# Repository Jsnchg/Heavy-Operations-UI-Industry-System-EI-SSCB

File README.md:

# Heavy-Operations-UI-Industry-System-EI-SSCB

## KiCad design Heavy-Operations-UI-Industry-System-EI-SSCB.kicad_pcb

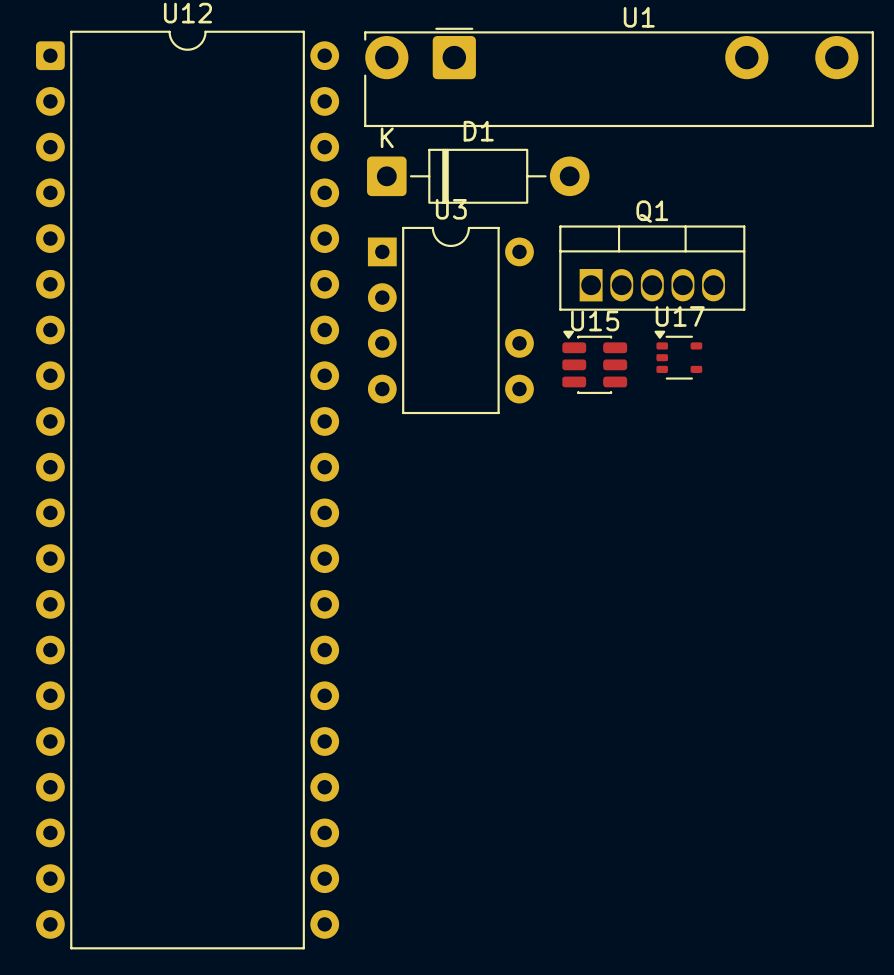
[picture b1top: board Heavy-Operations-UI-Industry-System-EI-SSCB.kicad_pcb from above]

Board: 2 copper layers, 7 parts (0 on the bottom side), 3 nets, no tracks yet.

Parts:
D1: 1N5817; D_DO-41_SOD81_P10.16mm_Horizontal
Q1: IPS6011PBF; TO-220-5_Vertical
U1: 34.81-7048; Finder_34.81
U3: NCP1072P065; DIP-8-N7_W7.62mm
U12: 8080; DIP-40_W15.24mm
U15: LM2665M6; SOT-23-6
U17: TLV172IDCK; SOT-353_SC-70-5

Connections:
unnamed: Q1.3 (VCC), U3.3 (GND), U3.8 (GND)
unnamed: U1.11, U15.1 (V+)
unnamed: U1.14, U17.4

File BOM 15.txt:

Heavy-Operations-UI-Industry-System-EI-SSCB
BOM 15

A. Solid-State Circuit Breaker
1. AC
2. NCP1250
3. NCP1072P065
4. IPS6011PBF
5. NIS3071
6. FAN65008B
7. 1N5817
8. NCP716B
9. NCP45520
10. N34TS108
11. D_Schottky_Filled x3
12. FXMA2102
13. D_Zener_Dual_CommonAnode_AKK
14. 34.81-7048
15. NCP51752
16. NCID9411
17. 8080
18. CAT24C512
19. NC7SZ57
20. D_Filled
21. LM2665M6 *
22. NCS2250
23. NCD98010
24. NCP51460
25. CAT3626
26. CAT5171
27. CAT9555
28. EMI1051
29. NCN26000
30. NCV7344
31. NCN5121
32. RSL15
33. ESDONCAN1LT

Note:
Component 21 is added to make the project more unique
